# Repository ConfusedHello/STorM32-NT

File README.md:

# STorM32-NT
A fork of boards from the STorM32 BGC project for my own purposes. I've panelised a few boards into a single panel to save PCB production costs as well as the pain of multiple orders.

The motor controller is based off the `STorM32 NT Motor v42EC G4` designed by [@KrattWorks](https://bitbucket.org/teamkrattworks/), details about modifications made can be found in this [README](/modules/Motor/README.md).

The STorM32 project is open source hardware, and is licenced under the terms of the [TAPR Open Hardware License](https://tapr.org/the-tapr-open-hardware-license/) as published by the Free Hardware Foundation.

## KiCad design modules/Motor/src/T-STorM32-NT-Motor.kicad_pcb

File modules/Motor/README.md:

# STorM32 NT Motor Controller
Custom version of the STorM32 NT Motor Controller modified from the STorM32 NT Motor v42EC G4.

Modifications made:
- Removed NTX bus from back for easier mounting
- Removed NTX bus pads from front as unused
- Removed unused SWDIO/SWCLK pins because I though they were unused for a external encoder and now I cant be bothered adding them back
- Moved some components to accomodate new NTX bus on front
- Cleaned up some traces
- Removed excess mounting holes/drill holes
- Added socket for connection to IMU and BGC

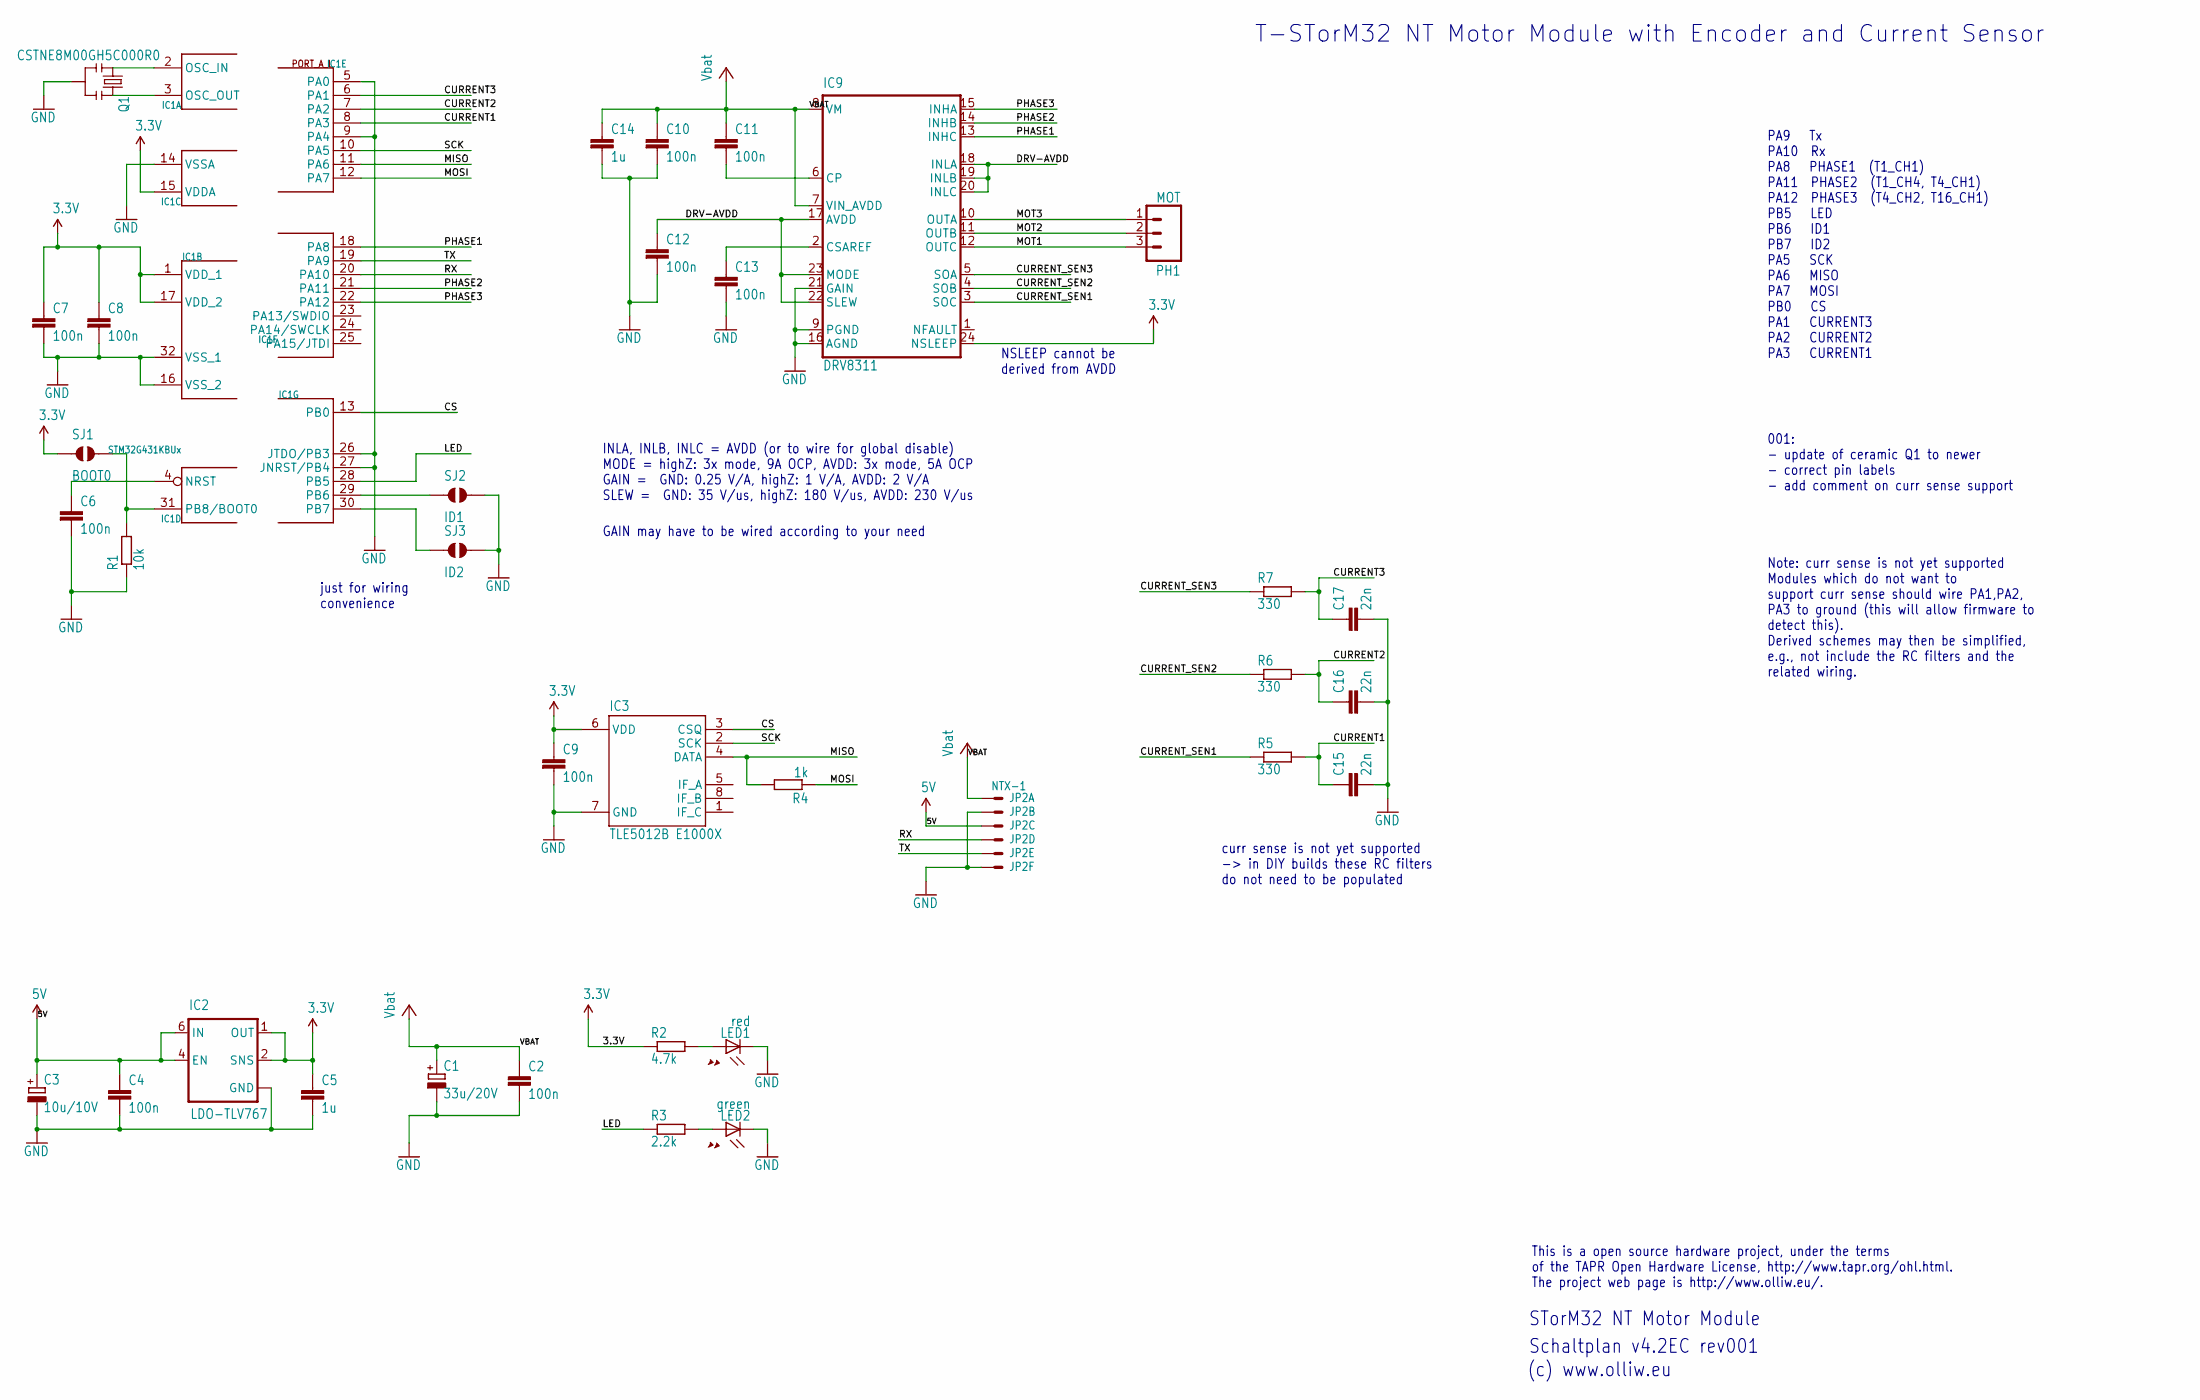
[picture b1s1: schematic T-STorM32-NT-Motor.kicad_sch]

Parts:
C1: 33u/20V; SMC_C
C2, C4: 100n; C0603
C3: 10u/10V; SMC_B
C5, C14: 1u; C0603
C6, C7, C8, C9, C10, C11, C12, C13: 100n; C0402
C15, C16, C17: 22n; C0402
IC1: STM32G431KBUx; UFQFPN32
IC2: LDO-TLV767; WSON-6-2X2
IC3: TLE5012B E1000X; SO08
IC9: DRV8311; QFN(WQFN)24-3X3-DRV8311
JP2: NTX-1; SM06B-SRSS-TB
LED1: red; CHIPLED_0603
LED2: green; CHIPLED_0603
PH1: MOT; 1X03_NO_SILK
Q1: CSTNE8M00GH5C000R0; RESONATOR-SMD
R1: 10k; R0402
R2: 4.7k; R0402
R3: 2.2k; R0402
R4: 1k; R0402
R5, R6, R7: 330; R0402
SJ1: BOOT0; SJ_2S-NO
SJ2: ID1; SJ_2S-NO
SJ3: ID2; SJ_2S-NO

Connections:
3.3V: C5.1, C7.1, C8.1, C9.1, IC1.1 (VDD_1), IC1.15 (VDDA), IC1.17 (VDD_2), IC2.1 (OUT), IC2.2 (SNS), IC3.6 (VDD), IC9.24 (NSLEEP), R2.1, SJ1.1
5V: C3.+, C4.1, IC2.4 (EN), IC2.6 (IN), JP2.3
CS: IC1.13 (PB0), IC3.3 (CSQ)
CURRENT1: C15.1, IC1.8 (PA3), R5.2
CURRENT2: C16.1, IC1.7 (PA2), R6.2
CURRENT3: C17.1, IC1.6 (PA1), R7.2
CURRENT_SEN1: IC9.3 (SOC), R5.1
CURRENT_SEN2: IC9.4 (SOB), R6.1
CURRENT_SEN3: IC9.5 (SOA), R7.1
DRV-AVDD: C12.1, IC9.17 (AVDD), IC9.18 (INLA), IC9.19 (INLB), IC9.20 (INLC), IC9.22 (SLEW), IC9.23 (MODE)
DRV-CP: C11.2, IC9.6 (CP)
DRV-CSAREF: C13.1, IC9.2 (CSAREF)
GND: C1.-, C2.2, C3.-, C4.2, C5.2, C6.2, C7.2, C8.2, C9.2, C10.2, C12.2, C13.2, C14.2, C15.2, C16.2, C17.2, IC1.5 (PA0), IC1.9 (PA4), IC1.14 (VSSA), IC1.16 (VSS_2), IC1.26 (JTDO/PB3), IC1.27 (JNRST/PB4), IC1.32 (VSS_1), IC2.3 (GND), IC2.5 (GND), IC2.7 (GND), IC3.7 (GND), IC9.9 (PGND), IC9.16 (AGND), IC9.21 (GAIN), JP2.2, JP2.6, LED1.C, LED2.C, Q1.2, R1.1, SJ2.2, SJ3.2
ID1: IC1.29 (PB6), SJ2.1
ID2: IC1.30 (PB7), SJ3.1
LED: IC1.28 (PB5), R3.1
MISO: IC1.11 (PA6), IC3.4 (DATA), R4.2
MOSI: IC1.12 (PA7), R4.1
MOT1: IC9.12 (OUTC), PH1.3
MOT2: IC9.11 (OUTB), PH1.2
MOT3: IC9.10 (OUTA), PH1.1
unnamed: C6.1, IC1.4 (NRST)
unnamed: IC1.31 (PB8/BOOT0), R1.2, SJ1.2
unnamed: IC1.2 (OSC_IN), Q1.1
unnamed: IC1.3 (OSC_OUT), Q1.3
unnamed: LED1.A, R2.2
unnamed: LED2.A, R3.2
PHASE1: IC1.18 (PA8), IC9.13 (INHC)
PHASE2: IC1.21 (PA11), IC9.14 (INHB)
PHASE3: IC1.22 (PA12), IC9.15 (INHA)
RX: IC1.20 (PA10), JP2.4
SCK: IC1.10 (PA5), IC3.2 (SCK)
SWCLK: IC1.24 (PA14/SWCLK)
SWDIO: IC1.23 (PA13/SWDIO)
TX: IC1.19 (PA9), JP2.5
VBAT: C1.+, C2.1, C10.1, C11.1, C14.1, IC9.7 (VIN_AVDD), IC9.8 (VM), JP2.1

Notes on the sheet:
INLA, INLB, INLC = AVDD (or to wire for global disable) MODE = highZ: 3x mode, 9A OCP, AVDD: 3x mode, 5A OCP GAIN = GND: 0.25 V/A, highZ: 1 V/A, AVDD: 2 V/A SLEW = GND: 35 V/us, highZ: 180 V/us, AVDD: 230 V/us
Note: curr sense is not yet supported Modules which do not want to support curr sense should wire PA1,PA2, PA3 to ground (this will allow firmware to detect this). Derived schemes may then be simplified, e.g., not include the RC filters and the related wiring.
STorM32 NT Motor Module
(c) www.olliw.eu
just for wiring convenience
T-STorM32 NT Motor Module with Encoder and Current Sensor
001: - update of ceramic Q1 to newer - correct pin labels - add comment on curr sense support
GAIN may have to be wired according to your need
Schaltplan v4.2EC rev001
PA9 Tx PA10 Rx PA8 PHASE1 (T1_CH1) PA11 PHASE2 (T1_CH4, T4_CH1) PA12 PHASE3 (T4_CH2, T16_CH1) PB5 LED PB6 ID1 PB7 ID2 PA5 SCK PA6 MISO PA7 MOSI PB0 CS PA1 CURRENT3 PA2 CURRENT2 PA3 CURRENT1
This is a open source hardware project, under the terms of the TAPR Open Hardware License, http://www.tapr.org/ohl.html. The project web page is http://www.olliw.eu/.
NSLEEP cannot be derived from AVDD
curr sense is not yet supported -> in DIY builds these RC filters do not need to be populated

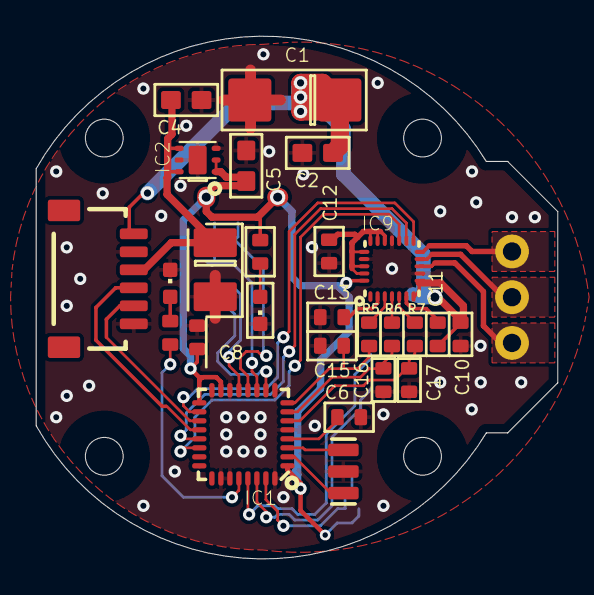
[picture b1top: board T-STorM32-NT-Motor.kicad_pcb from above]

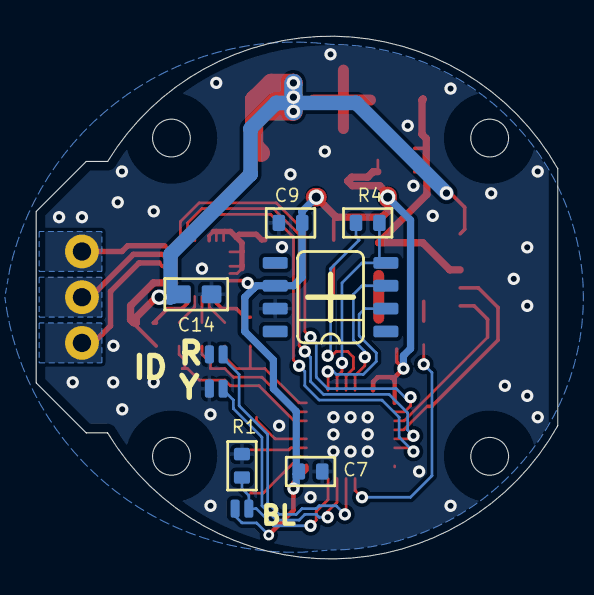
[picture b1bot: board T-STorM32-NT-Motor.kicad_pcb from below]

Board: 2 copper layers, 29.0 x 29.0 mm, 40 parts (9 on the bottom side), 34 nets.

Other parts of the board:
UNK_HOLE_0: dummyfp0
UNK_HOLE_1: dummyfp1
UNK_HOLE_2: dummyfp2
UNK_HOLE_3: dummyfp3

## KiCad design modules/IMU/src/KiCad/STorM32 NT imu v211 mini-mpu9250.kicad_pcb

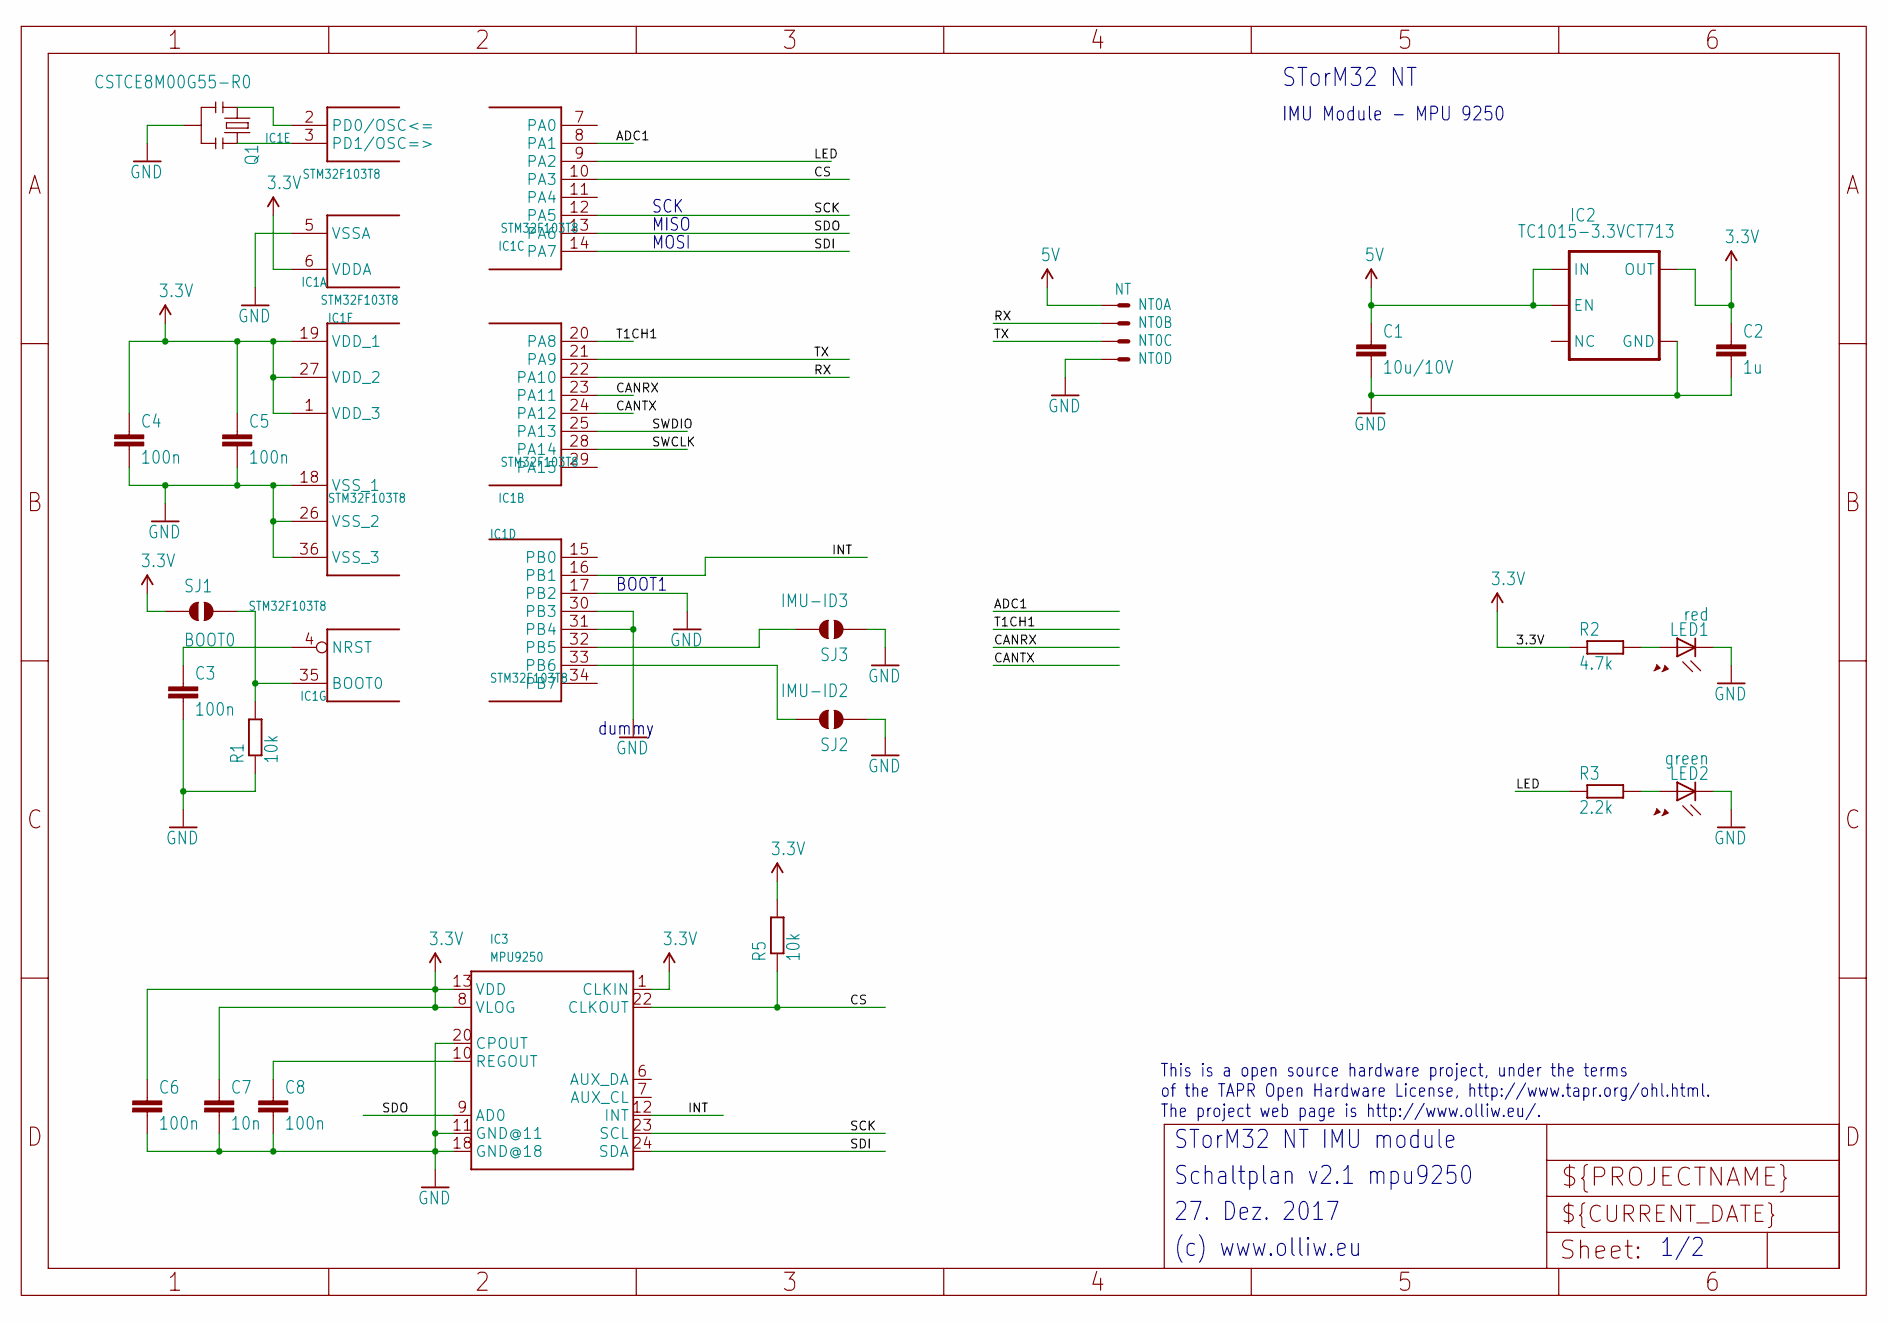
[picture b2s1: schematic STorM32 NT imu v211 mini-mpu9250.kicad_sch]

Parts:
C1: 10u/10V; C0805
C2: 1u; C0603
C3, C4, C5, C6, C8: 100n; C0402
C7: 10n; C0402
IC1: STM32F103T8; VFQFPN36
IC2: TC1015-3.3VCT713; SOT23-5
IC3: MPU9250; QFN-24-3X3
LED1: red; CHIPLED_0603
LED2: green; CHIPLED_0603
NT0: NT; SM04B-SRSS-TB
Q1: CSTCE8M00G55-R0; RESONATOR-SMD
R1, R5: 10k; R0402
R2: 4.7k; R0402
R3: 2.2k; R0402
SJ1: BOOT0; SJ_2S-NO
SJ2: IMU-ID2; SJ_2S-NO
SJ3: IMU-ID3; SJ_2S-NO

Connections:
3.3V: C2.1, C4.1, C5.1, C6.1, C7.1, IC1.1 (VDD_3), IC1.6 (VDDA), IC1.19 (VDD_1), IC1.27 (VDD_2), IC2.5 (OUT), IC3.1 (CLKIN), IC3.8 (VLOG), IC3.13 (VDD), R2.1, R5.2, SJ1.1
5V: C1.1, IC2.1 (IN), IC2.3 (EN), NT0.1
ADC1: IC1.8 (PA1)
CANRX: IC1.23 (PA11)
CANTX: IC1.24 (PA12)
CS: IC1.10 (PA3), IC3.22 (CLKOUT), R5.1
GND: C1.2, C2.2, C3.2, C4.2, C5.2, C6.2, C7.2, C8.2, IC1.5 (VSSA), IC1.17 (PB2), IC1.18 (VSS_1), IC1.26 (VSS_2), IC1.30 (PB3), IC1.31 (PB4), IC1.36 (VSS_3), IC2.2 (GND), IC3.11 (GND@11), IC3.18 (GND@18), IC3.20 (CPOUT), LED1.C, LED2.C, NT0.4, Q1.2, R1.1, SJ2.1, SJ3.1
INT: IC1.16 (PB1), IC3.12 (INT)
LED: IC1.9 (PA2), R3.1
unnamed: C3.1, IC1.4 (NRST)
unnamed: LED2.A, R3.2
unnamed: IC1.35 (BOOT0), R1.2, SJ1.2
unnamed: IC1.32 (PB5), SJ3.2
unnamed: IC1.2 (PD0/OSC<=), Q1.1
unnamed: IC1.3 (PD1/OSC=>), Q1.3
unnamed: IC1.33 (PB6), SJ2.2
unnamed: LED1.A, R2.2
unnamed: C8.1, IC3.10 (REGOUT)
RX: IC1.22 (PA10), NT0.2
SCK: IC1.12 (PA5), IC3.23 (SCL)
SDI: IC1.14 (PA7), IC3.24 (SDA)
SDO: IC1.13 (PA6), IC3.9 (AD0)
SWCLK: IC1.28 (PA14)
SWDIO: IC1.25 (PA13)
T1CH1: IC1.20 (PA8)
TX: IC1.21 (PA9), NT0.3

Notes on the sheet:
STorM32 NT IMU module
Schaltplan v2.1 mpu9250
MISO
MOSI
STorM32 NT
1/2
(c) www.olliw.eu
dummy
BOOT1
SCK
This is a open source hardware project, under the terms of the TAPR Open Hardware License, http://www.tapr.org/ohl.html. The project web page is http://www.olliw.eu/.
27. Dez. 2017
IMU Module - MPU 9250

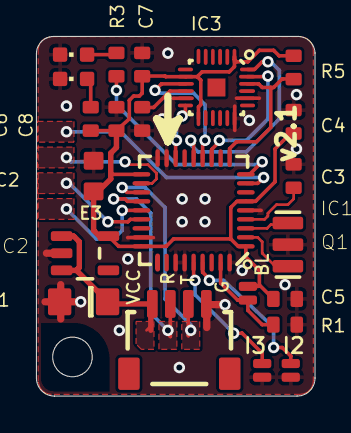
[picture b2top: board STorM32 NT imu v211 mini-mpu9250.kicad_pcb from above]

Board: 2 copper layers, 15.5 x 20.0 mm, 23 parts (0 on the bottom side), 20 nets.

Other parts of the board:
UNK_HOLE_0: dummyfp0

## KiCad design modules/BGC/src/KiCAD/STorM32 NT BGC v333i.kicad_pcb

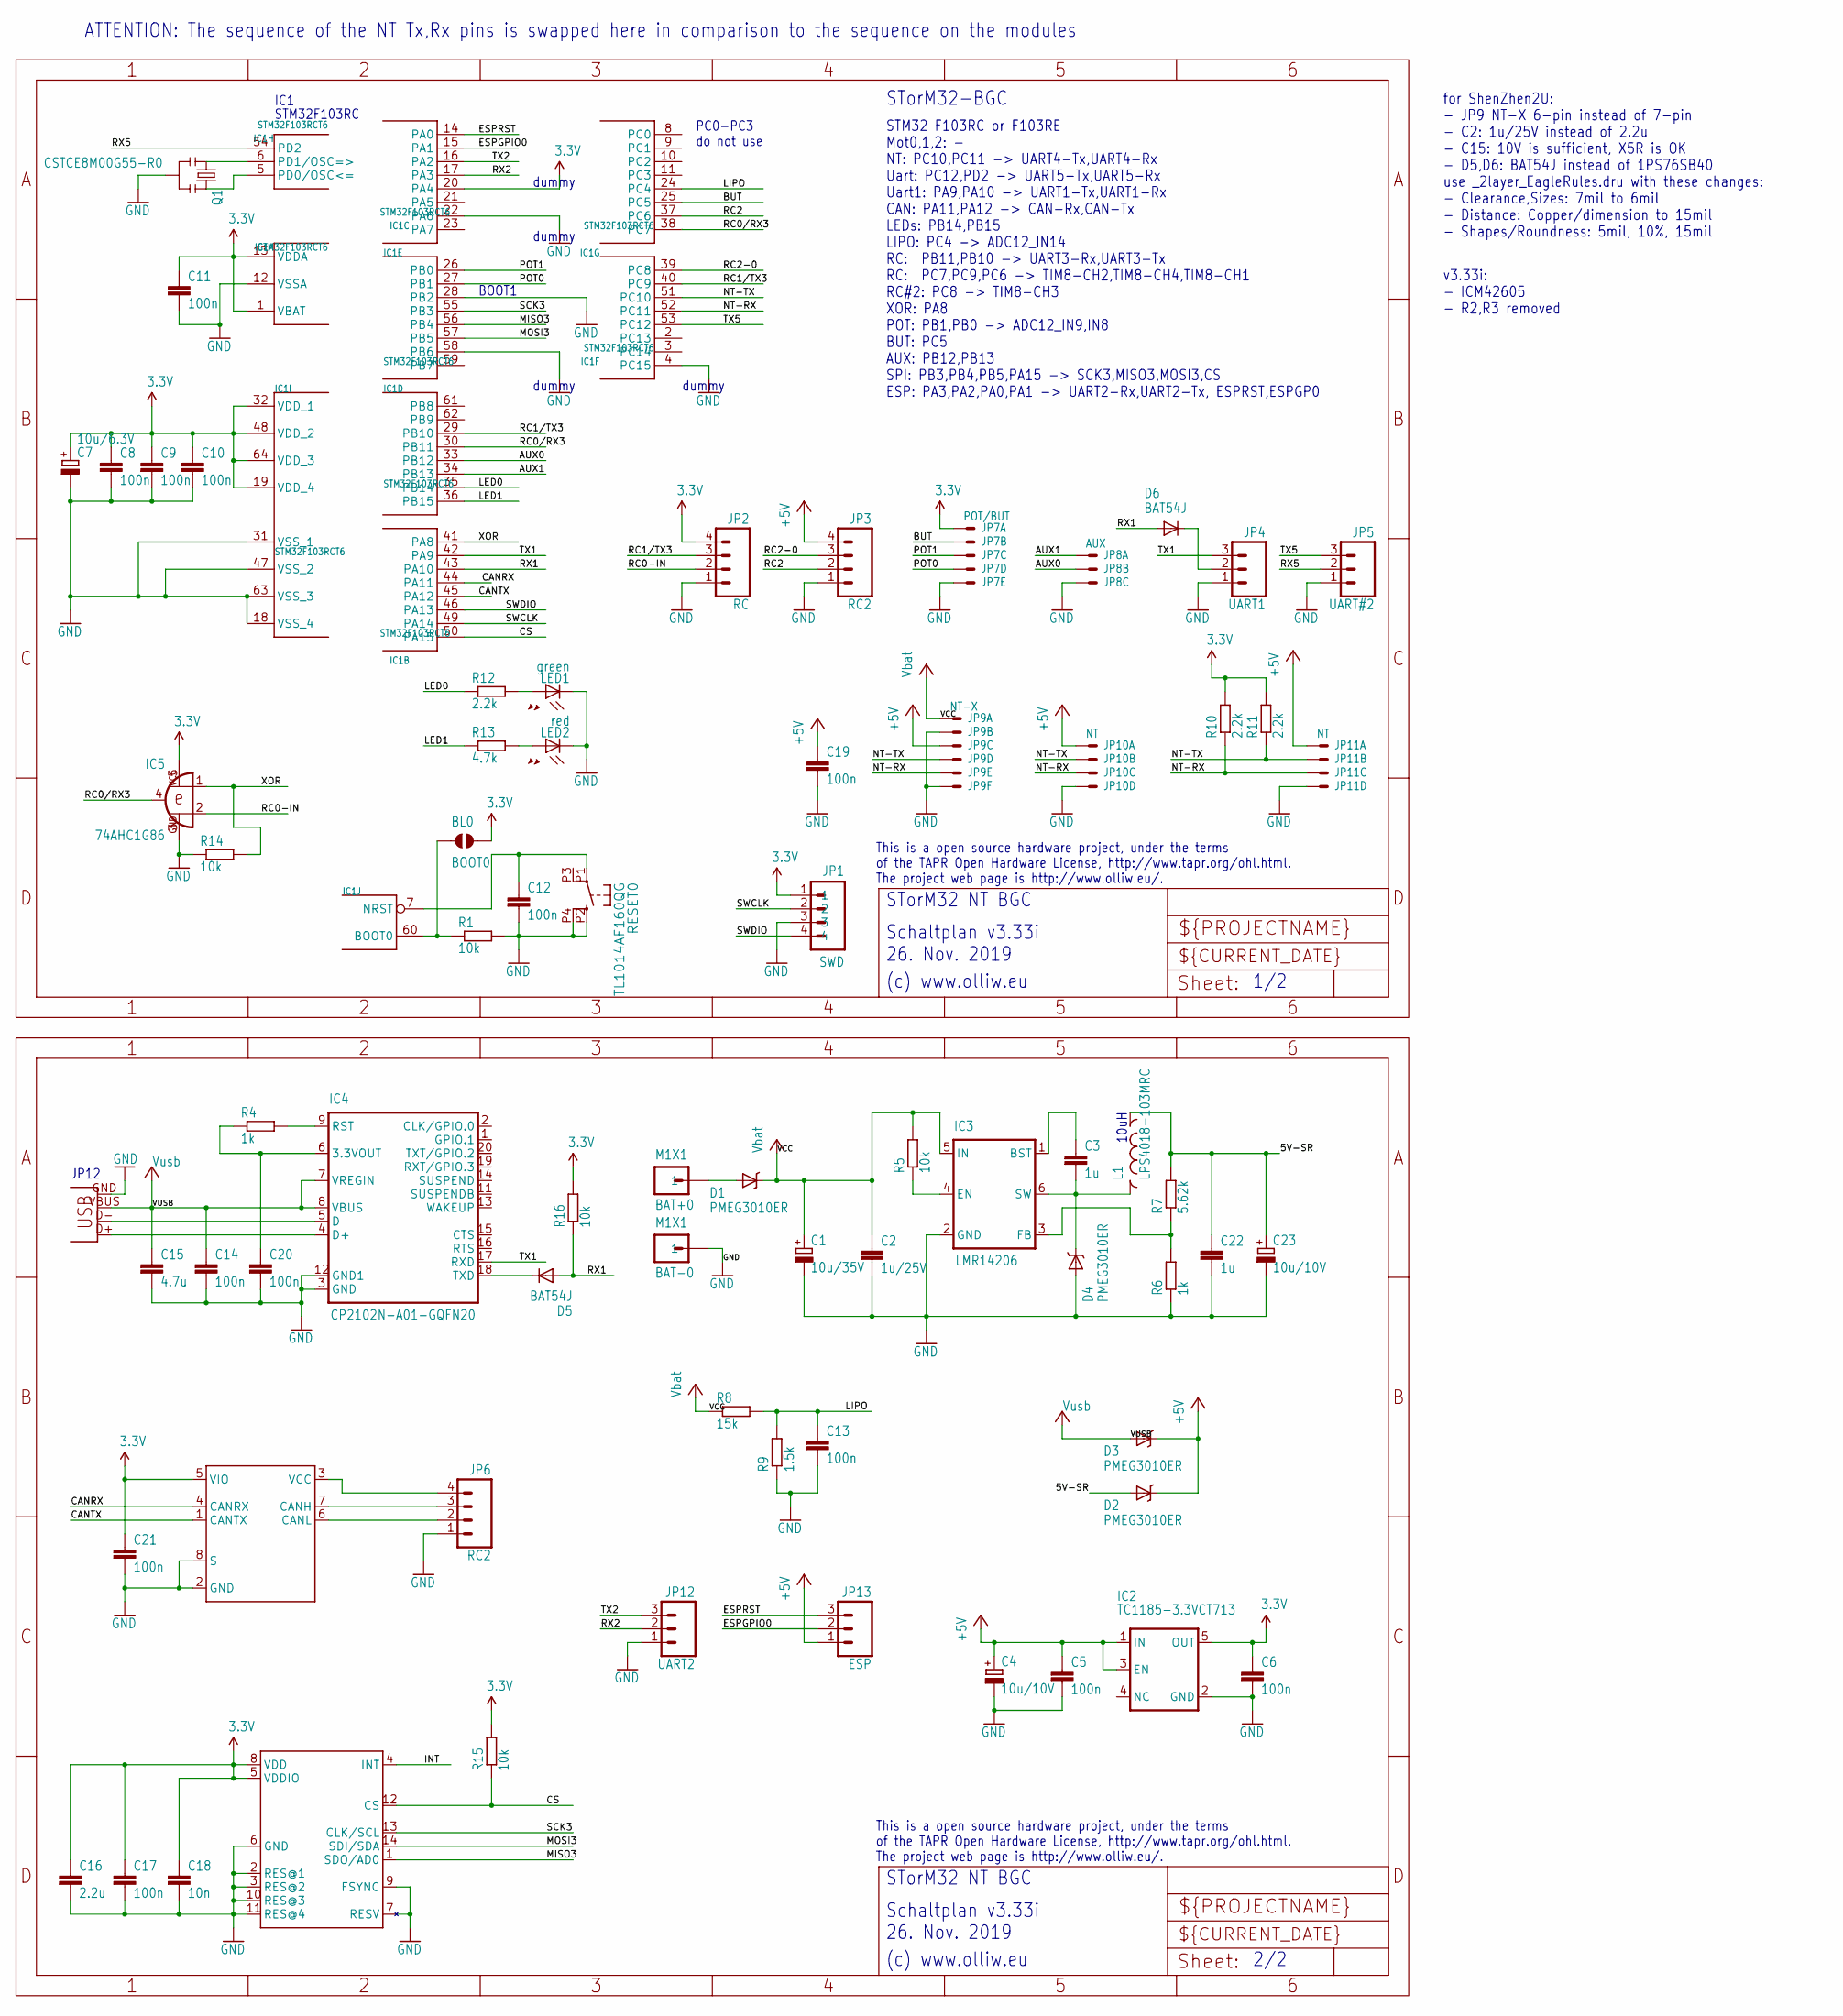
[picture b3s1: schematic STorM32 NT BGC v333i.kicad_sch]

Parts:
BAT+0: M1X1; 1X1_WITHOUT
BAT-0: M1X1; 1X1_WITHOUT
BL0: BOOT0; SJ_2S-NO
C1: 10u/35V; SMC_B
C2: 1u/25V; C0603
C3, C22: 1u; C0603
C4, C23: 10u/10V; SMC_A
C5: 100n; C0603
C6, C8, C9, C10, C11, C12, C13, C14, C17, C19, C20, C21: 100n; C0402
C7: 10u/6.3V; SMC_A
C15: 4.7u; C0603
C16: 2.2u; C0603
C18: 10n; C0402
D1, D2, D3, D4: PMEG3010ER; SOD123W-DIODE
D5, D6: BAT54J; SOD110-R
IC1: STM32F103RCT6; TQFP64
IC2: TC1185-3.3VCT713; SOT23-5
IC3: LMR14206; SOT23-6
IC4: CP2102N-A01-GQFN20; QFN20-CP2102N
IC5: 74AHC1G86; SOT23-5-VER1
IC6: ICM42605; LGA14-2.5X3
IC7: TJA1051TK/3; HVSON8
JP1: SWD; 4X1_1P27_OCT_BILEX
JP2: RC; 1X04_NO_SILK
JP3, JP6: RC2; 1X04_NO_SILK
JP4: UART1; 1X03_NO_SILK
JP5: UART#2; 1X03_NO_SILK
JP7: POT/BUT; SM05B-SRSS-TB
JP8: AUX; SM03B-SRSS-TB
JP9: NT-X; SM06B-SRSS-TB
JP10, JP11: NT; SM04B-SRSS-TB
JP12: UART2; 1X03_NO_SILK
JP13: ESP; 1X03_NO_SILK
L1: LPS4018-103MRC; L4X4
LED1: green; CHIPLED_0603
LED2: red; CHIPLED_0603
Q1: CSTCE8M00G55-R0; RESONATOR-SMD
R1, R5, R14, R15, R16: 10k; R0402
R4, R6: 1k; R0402
R7: 5.62k; R0402
R8: 15k; R0402
R9: 1.5k; R0402
R10, R11, R12: 2.2k; R0402
R13: 4.7k; R0402
RESET0: TL1014AF160QG; TACTILE-SWITCH-SMD-RIGHT-TL1014
USB0: Amphenol 10118192-0001LF; USB-MICROB

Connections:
3.3V: BL0.2, C6.1, C7.+, C8.1, C9.1, C10.1, C11.1, C16.1, C17.1, C18.1, C21.1, IC1.1 (VBAT), IC1.13 (VDDA), IC1.19 (VDD_4), IC1.20 (PA4), IC1.32 (VDD_1), IC1.48 (VDD_2), IC1.64 (VDD_3), IC2.5 (OUT), IC5.5 (VCC), IC6.5 (VDDIO), IC6.8 (VDD), IC7.5 (VIO), JP1.1, JP2.4, JP7.1, R10.2, R11.2, R15.2, R16.2
3.3V-CP2102: C20.1, IC4.6 (3.3VOUT), R4.1
5V-CAN-RAW: IC7.3 (VCC), JP6.4
5V-SR: C22.1, C23.+, D2.A, L1.1, R7.2
+5V: C4.+, C5.1, C19.1, D2.C, D3.C, IC2.1 (IN), IC2.3 (EN), JP3.4, JP9.3, JP10.1, JP11.1, JP13.1
AUX0: IC1.33 (PB12), JP8.2
AUX1: IC1.34 (PB13), JP8.1
BATP: BAT+0.1, D1.A
BOOT0: BL0.1, IC1.60 (BOOT0), R1.1
BUT: IC1.25 (PC5), JP7.2
CANH: IC7.7 (CANH), JP6.3
CANL: IC7.6 (CANL), JP6.2
CANRX: IC1.44 (PA11), IC7.4 (CANRX)
CANTX: IC1.45 (PA12), IC7.1 (CANTX)
CS: IC1.50 (PA15), IC6.12 (CS), R15.1
ESPGPIO0: IC1.15 (PA1), JP13.2
ESPRST: IC1.14 (PA0), JP13.3
GND: BAT-0.1, C1.-, C2.2, C4.-, C5.2, C6.2, C7.-, C8.2, C9.2, C10.2, C11.2, C12.2, C13.2, C14.2, C15.2, C16.2, C17.2, C18.2, C19.2, C20.2, C21.2, C22.2, C23.-, D4.A, IC1.4 (PC15), IC1.12 (VSSA), IC1.18 (VSS_4), IC1.22 (PA6), IC1.28 (PB2), IC1.31 (VSS_1), IC1.47 (VSS_2), IC1.58 (PB6), IC1.63 (VSS_3), IC2.2 (GND), IC3.2 (GND), IC4.3 (GND), IC4.12 (GND1), IC5.3 (GND), IC6.2 (RES@1), IC6.3 (RES@2), IC6.6 (GND), IC6.7 (RESV), IC6.9 (FSYNC), IC6.10 (RES@3), IC6.11 (RES@4), IC7.2 (GND), IC7.8 (S), JP1.3, JP2.1, JP3.1, JP4.1, JP5.1, JP6.1, JP7.5, JP8.3, JP9.2, JP9.6, JP10.4, JP11.4, JP12.1, LED1.C, LED2.C, Q1.2, R1.2, R6.1, R9.1, R14.1, RESET0.P2 (1), RESET0.P4 (2), USB0.GND
INT: IC6.4 (INT)
LED0: IC1.35 (PB14), R12.1
LED1: IC1.36 (PB15), R13.1
LIPO: C13.1, IC1.24 (PC4), R8.2, R9.2
MISO3: IC1.56 (PB4), IC6.1 (SDO/AD0)
MOSI3: IC1.57 (PB5), IC6.14 (SDI/SDA)
unnamed: IC4.5 (D-), USB0.D-
unnamed: IC4.4 (D+), USB0.D+
unnamed: IC3.4 (EN), R5.1
unnamed: LED1.A, R12.2
unnamed: LED2.A, R13.2
unnamed: IC1.5 (PD0/OSC<=), Q1.3
unnamed: IC1.6 (PD1/OSC=>), Q1.1
unnamed: C3.1, IC3.1 (BST)
unnamed: IC3.3 (FB), R6.2, R7.1
unnamed: C3.2, D4.C, IC3.6 (SW), L1.2
unnamed: D5.C, IC4.18 (TXD)
unnamed: D6.C, JP4.2
unnamed: IC4.9 (RST), R4.2
NRST: C12.1, IC1.7 (NRST), RESET0.P1 (3)
NT-RX: IC1.52 (PC11), JP9.5, JP10.3, JP11.3, R10.1
NT-TX: IC1.51 (PC10), JP9.4, JP10.2, JP11.2, R11.1
POT0: IC1.27 (PB1), JP7.4
POT1: IC1.26 (PB0), JP7.3
RC0-IN: IC5.2 (I1), JP2.2
RC0/RX3: IC1.30 (PB11), IC1.38 (PC7), IC5.4 (O)
RC1/TX3: IC1.29 (PB10), IC1.40 (PC9), JP2.3
RC2: IC1.37 (PC6), JP3.2
RC2-0: IC1.39 (PC8), JP3.3
RX1: D5.A, D6.A, IC1.43 (PA10), R16.1
RX2: IC1.17 (PA3), JP12.2
RX5: IC1.54 (PD2), JP5.2
SCK3: IC1.55 (PB3), IC6.13 (CLK/SCL)
SWCLK: IC1.49 (PA14), JP1.2
SWDIO: IC1.46 (PA13), JP1.4
TX1: IC1.42 (PA9), IC4.17 (RXD), JP4.3
TX2: IC1.16 (PA2), JP12.3
TX5: IC1.53 (PC12), JP5.3
VCC: C1.+, C2.1, D1.C, IC3.5 (IN), JP9.1, R5.2, R8.1
VUSB: C14.1, C15.1, D3.A, IC4.7 (VREGIN), IC4.8 (VBUS), USB0.VBUS
XOR: IC1.41 (PA8), IC5.1 (I0), R14.2

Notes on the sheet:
dummy
10uH
PC0-PC3 do not use
STM32F103RC
(c) www.olliw.eu
for ShenZhen2U: - JP9 NT-X 6-pin instead of 7-pin - C2: 1u/25V instead of 2.2u - C15: 10V is sufficient, X5R is OK - D5,D6: BAT54J instead of 1PS76SB40 use _2layer_EagleRules.dru with these changes: - Clearance,Sizes: 7mil to 6mil - Distance: Copper/dimension to 15mil - Shapes/Roundness: 5mil, 10%,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
1/2
v3.33i: - ICM42605 - R2,R3 removed
STorM32 NT BGC
This is a open source hardware project, under the terms of the TAPR Open Hardware License, http://www.tapr.org/ohl.html. The project web page is http://www.olliw.eu/.
2/2
IC1
BOOT1
JP12
Schaltplan v3.33i 26. Nov. 2019
STorM32-BGC
ATTENTION: The sequence of the NT Tx,Rx pins is swapped here in comparison to the sequence on the modules
STM32 F103RC or F103RE Mot0,1,2: - NT: PC10,PC11 -> UART4-Tx,UART4-Rx Uart: PC12,PD2 -> UART5-Tx,UART5-Rx Uart1: PA9,PA10 -> UART1-Tx,UART1-Rx CAN: PA11,PA12 -> CAN-Rx,CAN-Tx LEDs: PB14,PB15 LIPO: PC4 -> ADC12_IN14 RC: PB11,PB10 -> UART3-Rx,UART3-Tx RC: PC7,PC9,PC6 -> TIM8-CH2,TIM8-CH4,TIM8-CH1 RC#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

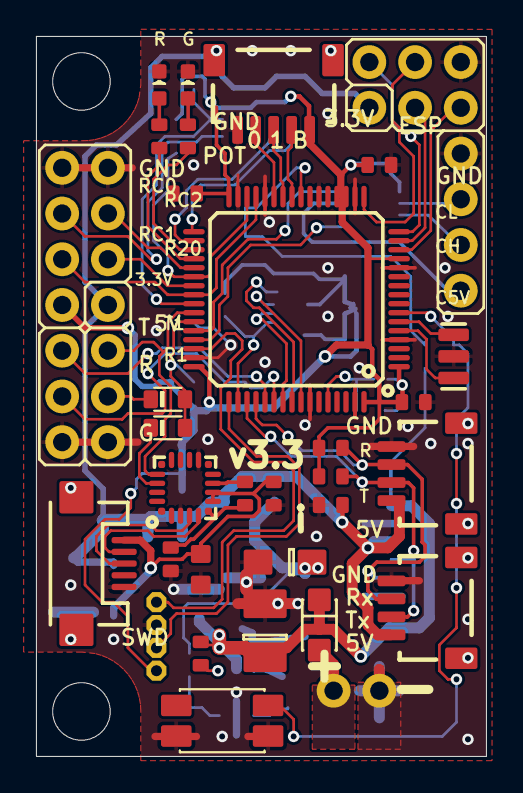
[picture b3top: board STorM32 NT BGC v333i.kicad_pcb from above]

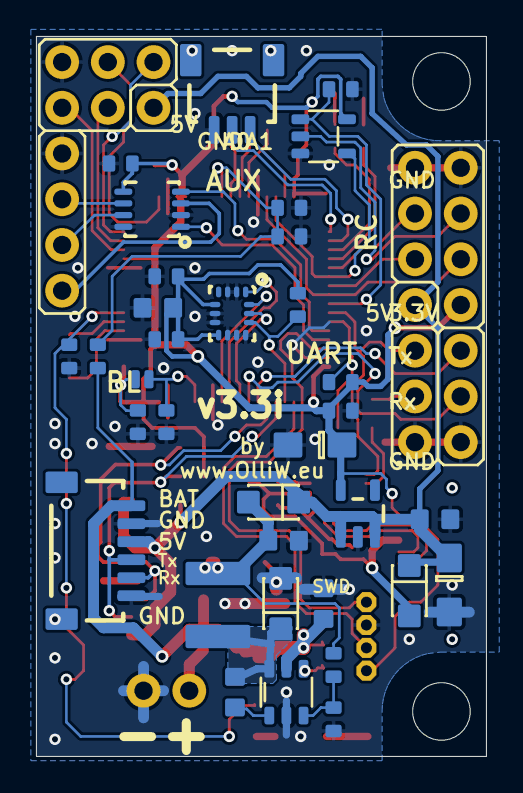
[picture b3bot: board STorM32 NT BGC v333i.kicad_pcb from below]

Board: 2 copper layers, 25.0 x 40.0 mm, 74 parts (34 on the bottom side), 58 nets.

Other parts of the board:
UNK_HOLE_0: dummyfp0
UNK_HOLE_1: dummyfp1

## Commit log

2025-05-29 Create LICENCE
2025-05-30 Add .gitignore for KiCad
2025-05-30 Add template files for BGC
2025-05-30 Upload motor controller
2025-06-02 Add JLCPCB DRC rules
2025-06-10 Update LICENCE
2025-06-10 Upload finalised modules
